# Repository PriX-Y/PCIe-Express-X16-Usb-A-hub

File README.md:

# Ucb-c to x4 usb-a hub

there some cool footrpints

and  schematic

idk i spend like 8h i need make 2 version becuse 1 verison dont work . i dont take screan shot when oi making 2 verion

so there is v1 what look like

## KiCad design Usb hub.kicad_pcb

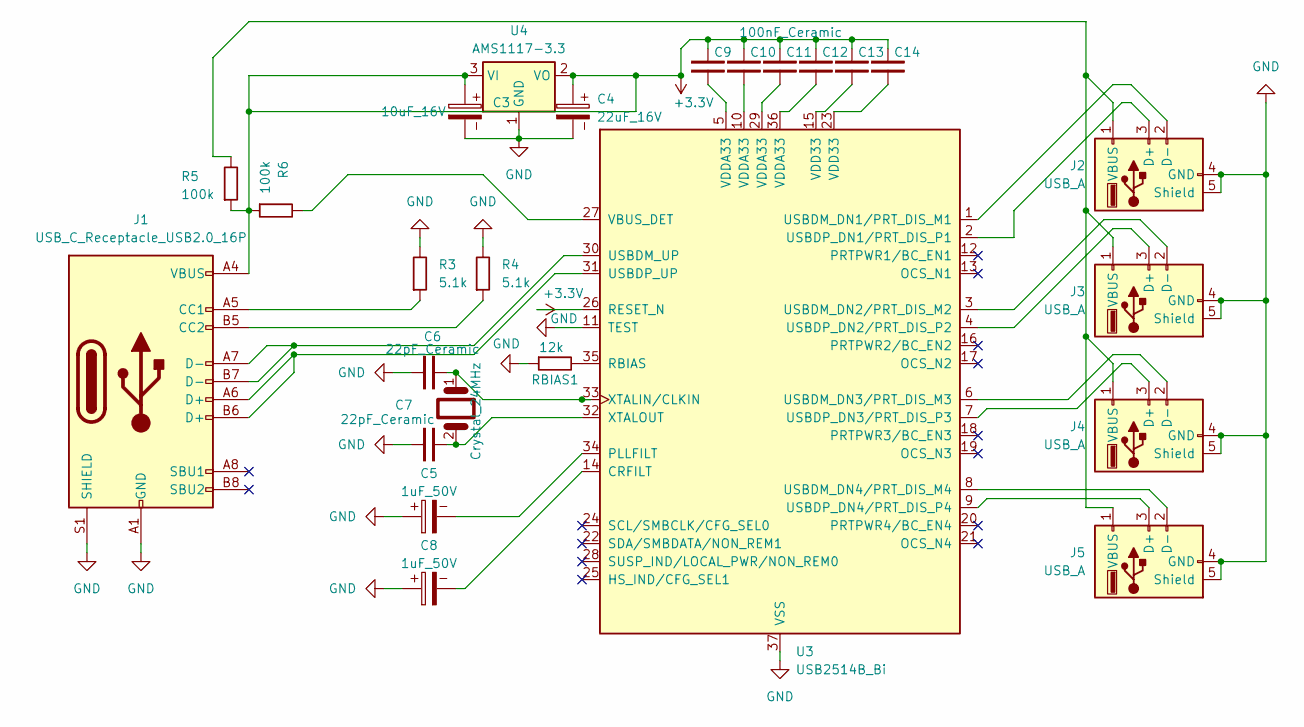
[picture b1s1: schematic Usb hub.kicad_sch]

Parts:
C3: 10uF_16V; CP_Radial_D5.0mm_P2.00mm
C4: 22uF_16V; CP_Radial_D4.0mm_P1.50mm
C5, C8: 1uF_50V; CP_Radial_D4.0mm_P1.50mm
C6, C7: 22pF_Ceramic; C_Disc_D5.0mm_W2.5mm_P2.50mm
C9, C10, C11, C12, C13, C14: 100nF_Ceramic; C_Disc_D5.0mm_W2.5mm_P2.50mm
J1: USB_C_Receptacle_USB2.0_16P; USB_C_Receptacle_GCT_USB4085
J2, J3, J4, J5: USB_A; USB_A_Molex_67643_Horizontal
R3, R4: 5.1k; R_Axial_DIN0207_L6.3mm_D2.5mm_P10.16mm_Horizontal
R5, R6: 100k; R_Axial_DIN0207_L6.3mm_D2.5mm_P10.16mm_Horizontal
RBIAS1: 12k; R_Axial_DIN0207_L6.3mm_D2.5mm_P10.16mm_Horizontal
U3: USB2514B_Bi; QFN-36-1EP_6x6mm_P0.5mm_EP3.7x3.7mm
U4: AMS1117-3.3; SOT-223-3_TabPin2
Y1: Crystal_24MHz; Crystal_HC49-4H_Vertical

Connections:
+3.3V: C3.1, C4.1, C9.2, C10.2, C11.2, C12.2, C13.2, C14.2, J1.A4 (VBUS), J1.A9 (VBUS), J1.B4 (VBUS), J1.B9 (VBUS), R5.1, R6.1, U3.26 (RESET_N), U4.2 (VO), U4.3 (VI)
GND: C3.2, C4.2, C5.1, C6.1, C7.1, C8.1, J1.A1 (GND), J1.A12 (GND), J1.B1 (GND), J1.B12 (GND), J1.S1 (SHIELD), J2.4 (GND), J2.5 (Shield), J3.4 (GND), J3.5 (Shield), J4.4 (GND), J4.5 (Shield), J5.4 (GND), J5.5 (Shield), R3.2, R4.2, RBIAS1.1, U3.11 (TEST), U3.37 (VSS), U4.1 (GND)
unnamed: C9.1, U3.5 (VDDA33)
unnamed: C10.1, U3.10 (VDDA33)
unnamed: C11.1, U3.29 (VDDA33)
unnamed: C12.1, U3.36 (VDDA33)
unnamed: C13.1, U3.15 (VDD33)
unnamed: C14.1, U3.23 (VDD33)
unnamed: J1.A5 (CC1), R3.1
unnamed: J1.B5 (CC2), R4.1
unnamed: J2.3 (D+), U3.2 (USBDP_DN1/PRT_DIS_P1)
unnamed: J2.2 (D-), U3.1 (USBDM_DN1/PRT_DIS_M1)
unnamed: J2.1 (VBUS), J3.1 (VBUS), J4.1 (VBUS), J5.1 (VBUS), R5.2
unnamed: J3.3 (D+), U3.4 (USBDP_DN2/PRT_DIS_P2)
unnamed: J3.2 (D-), U3.3 (USBDM_DN2/PRT_DIS_M2)
unnamed: J4.3 (D+), U3.7 (USBDP_DN3/PRT_DIS_P3)
unnamed: J4.2 (D-), U3.6 (USBDM_DN3/PRT_DIS_M3)
unnamed: J5.3 (D+), U3.9 (USBDP_DN4/PRT_DIS_P4)
unnamed: J5.2 (D-), U3.8 (USBDM_DN4/PRT_DIS_M4)
unnamed: C8.2, U3.14 (CRFILT)
unnamed: C5.2, U3.34 (PLLFILT)
unnamed: RBIAS1.2, U3.35 (RBIAS)
unnamed: J1.A7 (D-), J1.B7 (D-), U3.30 (USBDM_UP)
unnamed: J1.A6 (D+), J1.B6 (D+), U3.31 (USBDP_UP)
unnamed: R6.2, U3.27 (VBUS_DET)
unnamed: C6.2, U3.33 (XTALIN/CLKIN), Y1.1
unnamed: C7.2, U3.32 (XTALOUT), Y1.2

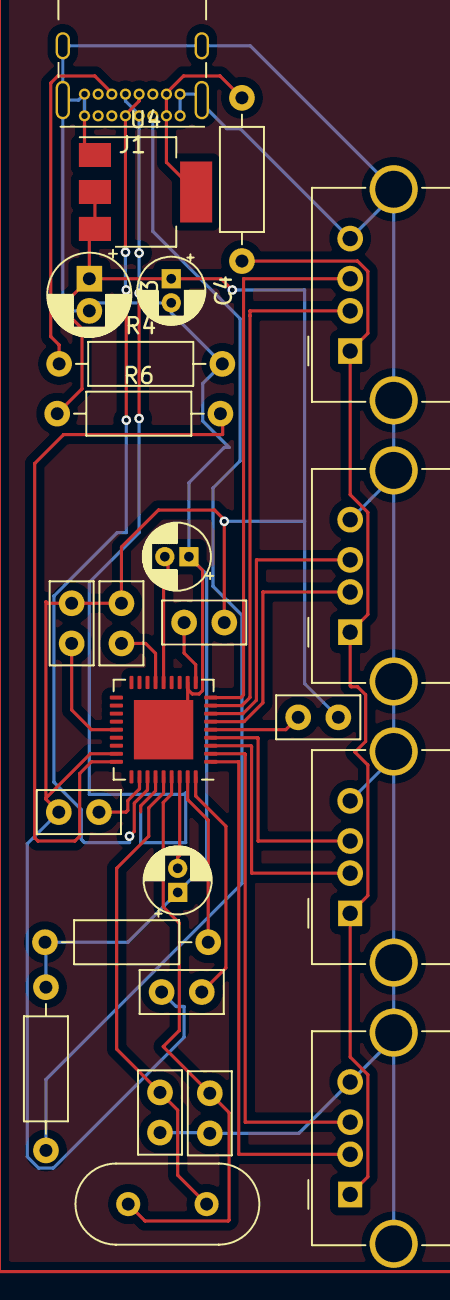
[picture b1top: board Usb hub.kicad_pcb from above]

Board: 2 copper layers, 25 parts (0 on the bottom side), 27 nets.

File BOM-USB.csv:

,Id,Footprint,Liczba,Oznaczenie
1,Oznaczenie,C_Disc_D5.0mm_W2.5mm_P2.50mm,6,100nF_Ceramic
2,"J3,J4,J2,J5",USB_A_Molex_67643_Horizontal,4,USB_A
3,Y1,Crystal_HC49-4H_Vertical,1,Crystal_24MHz
4,U4,SOT-223-3_TabPin2,1,AMS1117-3.3
5,U3,QFN-36-1EP_6x6mm_P0.5mm_EP3.7x3.7mm,1,USB2514B_Bi
6,RBIAS1,R_Axial_DIN0207_L6.3mm_D2.5mm_P10.16mm_Horizontal,1,12k
7,"R6,R5",R_Axial_DIN0207_L6.3mm_D2.5mm_P10.16mm_Horizontal,2,100k
8,"R4,R3",R_Axial_DIN0207_L6.3mm_D2.5mm_P10.16mm_Horizontal,2,5.1k
9,J1,USB_C_Receptacle_GCT_USB4085,1,USB_C_Receptacle_USB2.0_16P
10,"C8,C5",CP_Radial_D4.0mm_P1.50mm,2,1uF_50V
11,"C7,C6",C_Disc_D5.0mm_W2.5mm_P2.50mm,2,22pF_Ceramic
12,C4,CP_Radial_D4.0mm_P1.50mm,1,22uF_16V
13,C3,CP_Radial_D5.0mm_P2.00mm,1,10uF_16V
